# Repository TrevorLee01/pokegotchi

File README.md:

# Pokegotchi
tamagotchi project by Trevor Lee

ONSHAPE LINK: https://cad.onshape.com/documents/4788cfc2c41ccbd3b3bb658b/w/c8008663c56e0ba217e7b347/e/ed1d7d4fd3640974190b7d9b?renderMode=0&uiState=6a3ac660f6d661f4c890654a

BOM INCLUDED IN THE FILES! "BOM.csv", bottom of this README, or: https://docs.google.com/spreadsheets/d/1ZSV7nk1klidvS7acBAQEKFNUl_y9adzhBfaWMznL6cg/edit?gid=0#gid=0

______________

# What is a Pokegotchi?

This pokegotchi comes with 3 whole pokemons
- Snorlax
- Solosis
- Eevee
However, Eevee comes with 5 different types of Eeveelution depending on the exact environment (a secret). Play to find out which eeveelution you end up getting!

The possible 5 includes:
- umbreon
- leafeon
- slyveon
- glaceon
- espeon

____
# Features

The unique features of this tamagotchi are
- internal clock ( to tell between day and night)
- LDR (to tell how dark it is)

(and a completely different ESP32 :D)

____
# Why did I make it?

Through my entire childhood, I've always been into some type of media related to Pokemon. Despite being it a common hobby or interest, that never discouraged me to discontinue the love I have for Pokemon. 
I think it's such a fundamental piece to my development and I want to physically manifest the fondness by utilizing the hardware opportunity given by fallout. 

____
# Pictures‼️

Here is the pcb.

Here is the CAD.

Here is the render.

____
# How It Works ╰(°▽°)╯

Turn the Pokegotchi on and select one out of three Pokémon that you want to take care of: Snorlax, Solosis, or Eevee.

The built-in real-time clock (RTC) will help you keep track of the current time, enabling the device to know whether it is day or night. In addition, the light-dependent resistor (LDR) will detect how bright the surrounding environment is and make your Pokémon respond accordingly.

Should you pick Eevee, it will evolve into one of five unique Eeveelutions, depending both on your in-game actions and some hidden environmental factors.

Use the buttons on the Pokegotchi to navigate through the menus.

____
# How to Build Your Own Pokegotchi :D

1. Print the Case: Download the .step files from the repository and use a 3D printer to print the front case and back case.

2. Solder the Components: Solder all the components to the custom PCB, including the ESP32, RTC IC, light sensor (LDR), display, buttons, and other hardware as specified in the bill of materials.

3. Place the Hardware: Install the PCB inside the printed case using 2 M3x10 screws, and then secure the top of the case using 3 M3x5 screws. Don't forget to place the battery inside its pocket, and connect it to the pinheader.

4. Upload the Firmware: Download the .ino file from the repository and flash Pokegotchi firmware onto the ESP32.

5. Get Ready for an Exciting Journey: Turn on the device, select a Pokémon, and start training your Pokegotchi!

____
# BOM

POKEGOTCHI BILL OF MATERIALS,,,,,
 Total Cost ,,,,,
 $ 44.40 ,,,,,
,,,,,
Item, Indiv Costs ,Quanities, Cost ,Links to Order,Additional Notes
ESP32-S3-WROOM-1-N16R8 MCU, $ 6.76 ,1, $ 6.76 ,https://www.digikey.com/en/products/detail/espressif-systems/ESP32-S3-WROOM-1-N16R8/16162642,
TYPE-C-31-M-12 USB-C Receptable, $ 0.19 ,5, $ 0.93 ,https://www.lcsc.com/product-detail/C165948.html?s_z=n_q_korean%2520hroparts%2520elec%2520type-c-31-m-12&spm=wm.fly.bg.1.xh&lcsc_vid=R1cKX1cFEVUKX1ECR1FdBlRQFlAMUwFUElkPUwcDQwAxVlNeRlhZV1dRQ1dZUDsOAxUeFF5JWBYZEEoKFBINSQcJGk4%3D,"4 extra, MOQ 5"
XHXDZ 1207-P6.5MM Buzzer, $ 0.50 ,10, $ 5.03 ,https://www.aliexpress.us/item/3256810135642750.html,"9 extra, MOQ 10"
MCP73831T-2ATI/OT Charger, $ 0.76 ,1, $ 0.76 ,https://www.digikey.com/en/products/detail/microchip-technology/MCP73831T-2ATI-OT/964303?s=N4IgTCBcDaILYGMAOB2AzADjQRgCoFowBDAFwEsB6AexJAF0BfIA,
AP2112K-3.3TRG1 Voltage Regulator, $ 0.25 ,1, $ 0.25 ,https://www.digikey.com/en/products/detail/diodes-incorporated/AP2112K-3-3TRG1/4470746?s=N4IgTCBcDaIIYAcwEZlgNYFoDMA6bALgE4DmyIAugL5A,
1825910-6 Tactile Switch, $ 0.13 ,3, $ 0.39 ,https://www.digikey.com/en/products/detail/te-connectivity-alcoswitch-switches/1825910-6/1632536,
TS-104-T-A Connector, $ 1.06 ,1, $ 1.06 ,https://www.digikey.com/en/products/detail/samtec-inc/TS-104-T-A/1105490,
M20-9990246 Connector, $ 0.10 ,1, $ 0.10 ,https://www.digikey.com/en/products/detail/harwin-inc/M20-9990246/3728226?s=N4IgTCBcDaILZgAwFoCc7FgCwDYQF0BfIA,
1825910-6 Tactile Switch, $ 0.13 ,3, $ 0.39 ,https://www.digikey.com/en/products/detail/te-connectivity-alcoswitch-switches/1825910-6/1632536,
RC0805JR-075K1L Resistor, $ 0.10 ,2, $ 0.20 ,https://www.digikey.com/en/products/detail/yageo/RC0805JR-075K1L/728338,
RC0805FR-072KL Resistor, $ 0.10 ,1, $ 0.10 ,https://www.digikey.com/en/products/detail/yageo/RC0805FR-072KL/727664,
RC0805FR-0710KL Resistor, $ 0.10 ,3, $ 0.30 ,https://www.digikey.com/en/products/detail/yageo/RC0805FR-0710KL/727535,
RC0805FR-074K7L Resistor, $ 0.10 ,2, $ 0.20 ,https://www.digikey.com/en/products/detail/yageo/RC0805FR-074K7L/727929,
GL12528 LDR, $ 0.31 ,5, $ 1.56 ,https://www.lcsc.com/product-detail/C559386.html?s_z=s_p_GL12528&spm=wm.fly.bg.0.xh&lcsc_vid=Q1kKUVEAQgNbV11QQgQPV1FVRVkLV11TE1hXUwBfEgcxVlNeRVBZUFxXQlhbVjsOAxUeFF5JWBYZEEoKFBINSQcJGk4dAgUUFAk%3D,"4 extra, MOQ 5"
CL21B105KAFNNNE Capacitor, $ 0.10 ,1, $ 0.10 ,https://www.digikey.com/en/products/detail/samsung-electro-mechanics/CL21B105KAFNNNE/3886724,
CL21A475KAQNNNE Capacitor, $ 0.11 ,2, $ 0.22 ,https://www.digikey.com/en/products/detail/samsung-electro-mechanics/CL21A475KAQNNNE/3886902,
HS96L03W2C03 Screen, $ 1.87 ,1, $ 1.87 ,https://www.aliexpress.us/item/2251832337475453.html,
DS3231MZ+TRL Clock, $ 12.68 ,1, $ 12.68 ,https://www.digikey.com/en/products/detail/analog-devices-inc-maxim-integrated/DS3231MZ-TRL/2754408,
Battery, $ 6.20 ,1, $ 6.20 ,https://www.aliexpress.us/item/3256808658204287.html,
PCB, $ 0.40 ,5, $ 2.00 ,https://cart.jlcpcb.com/quote?stencilLayer=2&stencilWidth=100&stencilLength=100&stencilCounts=5&plateType=1&spm=Jlcpcb.Homepage.1010,
PLA Housing, $ -   ,, $ -   ,,
M3 x 10mm Socket Cap Head Screws, $ 0.75 ,2, $ 1.50 ,https://accu-components.com/us/metric-cap-head-screws/16004-SSCF-M3-10-12-9,
M3 x 5mm Socket Cap Head Screws, $ 0.45 ,4, $ 1.80 ,https://accu-components.com/us/metric-cap-head-screws/16001-SSCF-M3-5-12-9,4 is cheaper than 3

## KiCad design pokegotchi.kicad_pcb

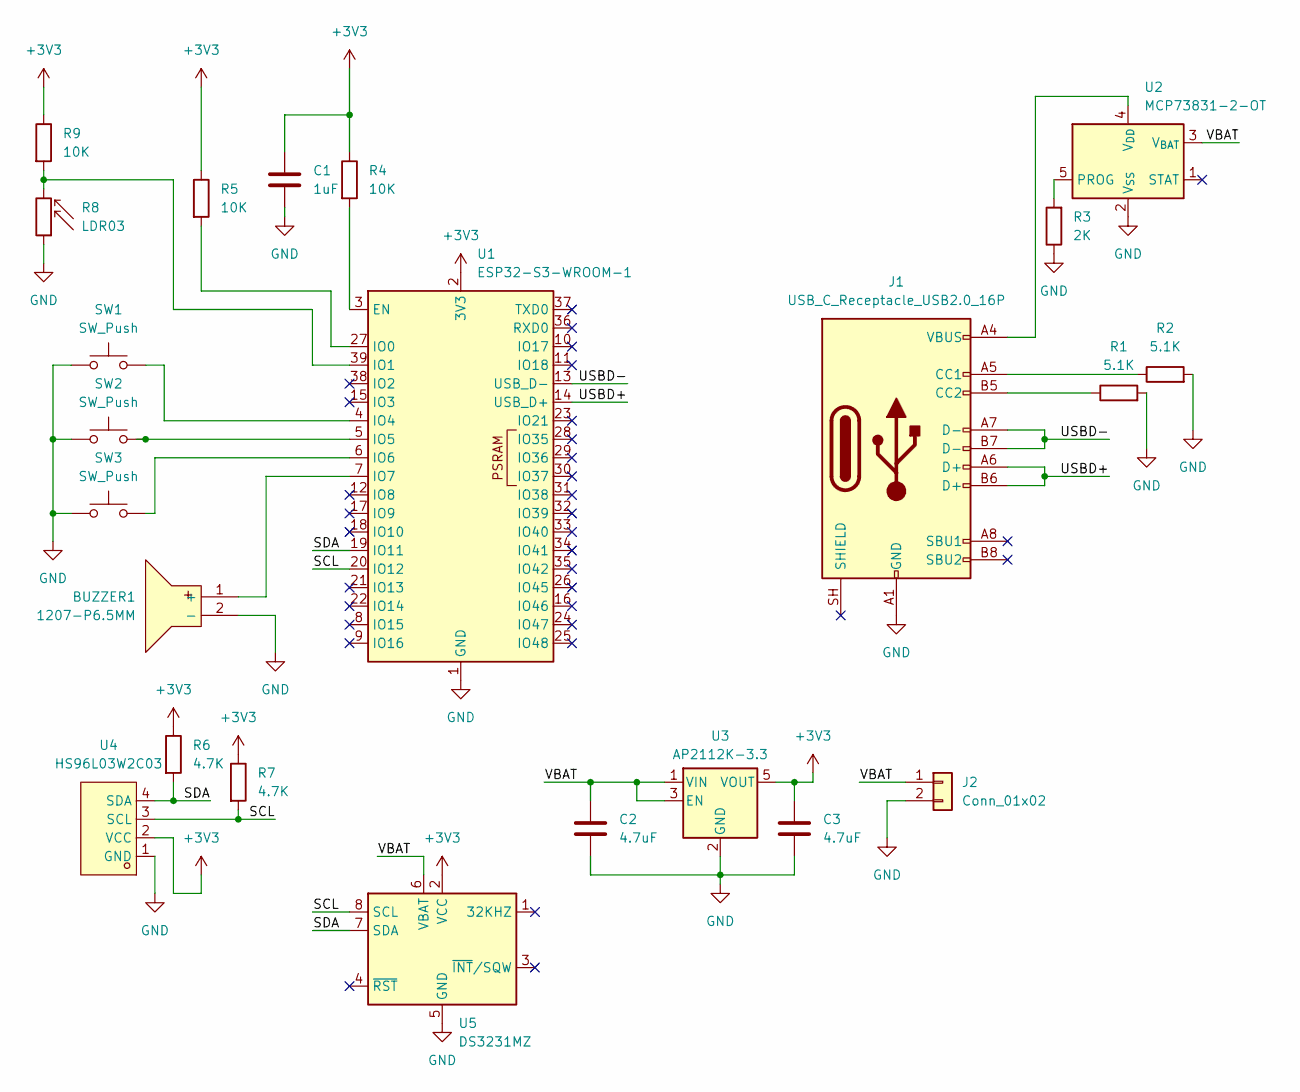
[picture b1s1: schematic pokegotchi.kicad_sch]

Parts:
BUZZER1: 1207-P6.5MM; BUZ-TH_BD12.5-P6.50-D1.4; MPN 1207-P6.5MM; LCSC Part C49246964
C1: 1uF; C_0805_2012Metric
C2, C3: 4.7uF; C_0805_2012Metric
J1: USB_C_Receptacle_USB2.0_16P; USB_C_Receptacle_HRO_TYPE-C-31-M-12
J2: Conn_01x02; PinHeader_1x02_P2.54mm_Vertical
R1, R2: 5.1K; R_0805_2012Metric
R3: 2K; R_0805_2012Metric
R4, R5, R9: 10K; R_0805_2012Metric
R6, R7: 4.7K; R_0805_2012Metric
R8: LDR03; R_LDR_10x8.5mm_P7.6mm_Vertical
SW1, SW2, SW3: SW_Push; SW_PUSH_6mm
U1: ESP32-S3-WROOM-1
U2: MCP73831-2-OT; SOT-23-5
U3: AP2112K-3.3; SOT-23-5
U4: HS96L03W2C03; OLED-TH_L27.8-W27.2-P2.54_C9900033791; MPN HS96L03W2C03; LCSC Part C5248080
U5: DS3231MZ; SOIC-8_3.9x4.9mm_P1.27mm

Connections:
+3V3: C1.1, C3.1, R4.1, R5.1, R6.1, R7.1, R9.1, U1.2 (3V3), U3.5 (VOUT), U4.2 (VCC), U5.2 (VCC)
/SCL: R7.2, U1.20 (IO12), U4.3 (SCL), U5.8 (SCL)
/SDA: R6.2, U1.19 (IO11), U4.4 (SDA), U5.7 (SDA)
/USBD+: J1.A6 (D+), J1.B6 (D+), U1.14 (USB_D+)
/USBD-: J1.A7 (D-), J1.B7 (D-), U1.13 (USB_D-)
/VBAT: C2.1, J2.1, U2.3 (V_{BAT}), U3.1 (VIN), U3.3 (EN), U5.6 (VBAT)
GND: BUZZER1.2 (-), C1.2, C2.2, C3.2, J1.A1 (GND), J1.A12 (GND), J1.B1 (GND), J1.B12 (GND), J2.2, R1.2, R2.2, R3.1, R8.1, SW1.1, SW2.1, SW3.1, U1.1 (GND), U1.40 (GND), U1.41 (GND), U2.2 (V_{SS}), U3.2 (GND), U4.1 (GND), U5.5 (GND)
unnamed: BUZZER1.1 (+), U1.7 (IO7)
unnamed: J1.A5 (CC1), R2.1
unnamed: J1.B5 (CC2), R1.1
unnamed: R4.2, U1.3 (EN)
unnamed: R5.2, U1.27 (IO0)
unnamed: R8.2, R9.2, U1.39 (IO1)
unnamed: SW1.2, U1.4 (IO4)
unnamed: SW2.2, U1.5 (IO5)
unnamed: SW3.2, U1.6 (IO6)
unnamed: R3.2, U2.5 (PROG)
unnamed: J1.A4 (VBUS), J1.A9 (VBUS), J1.B4 (VBUS), J1.B9 (VBUS), U2.4 (V_{DD})

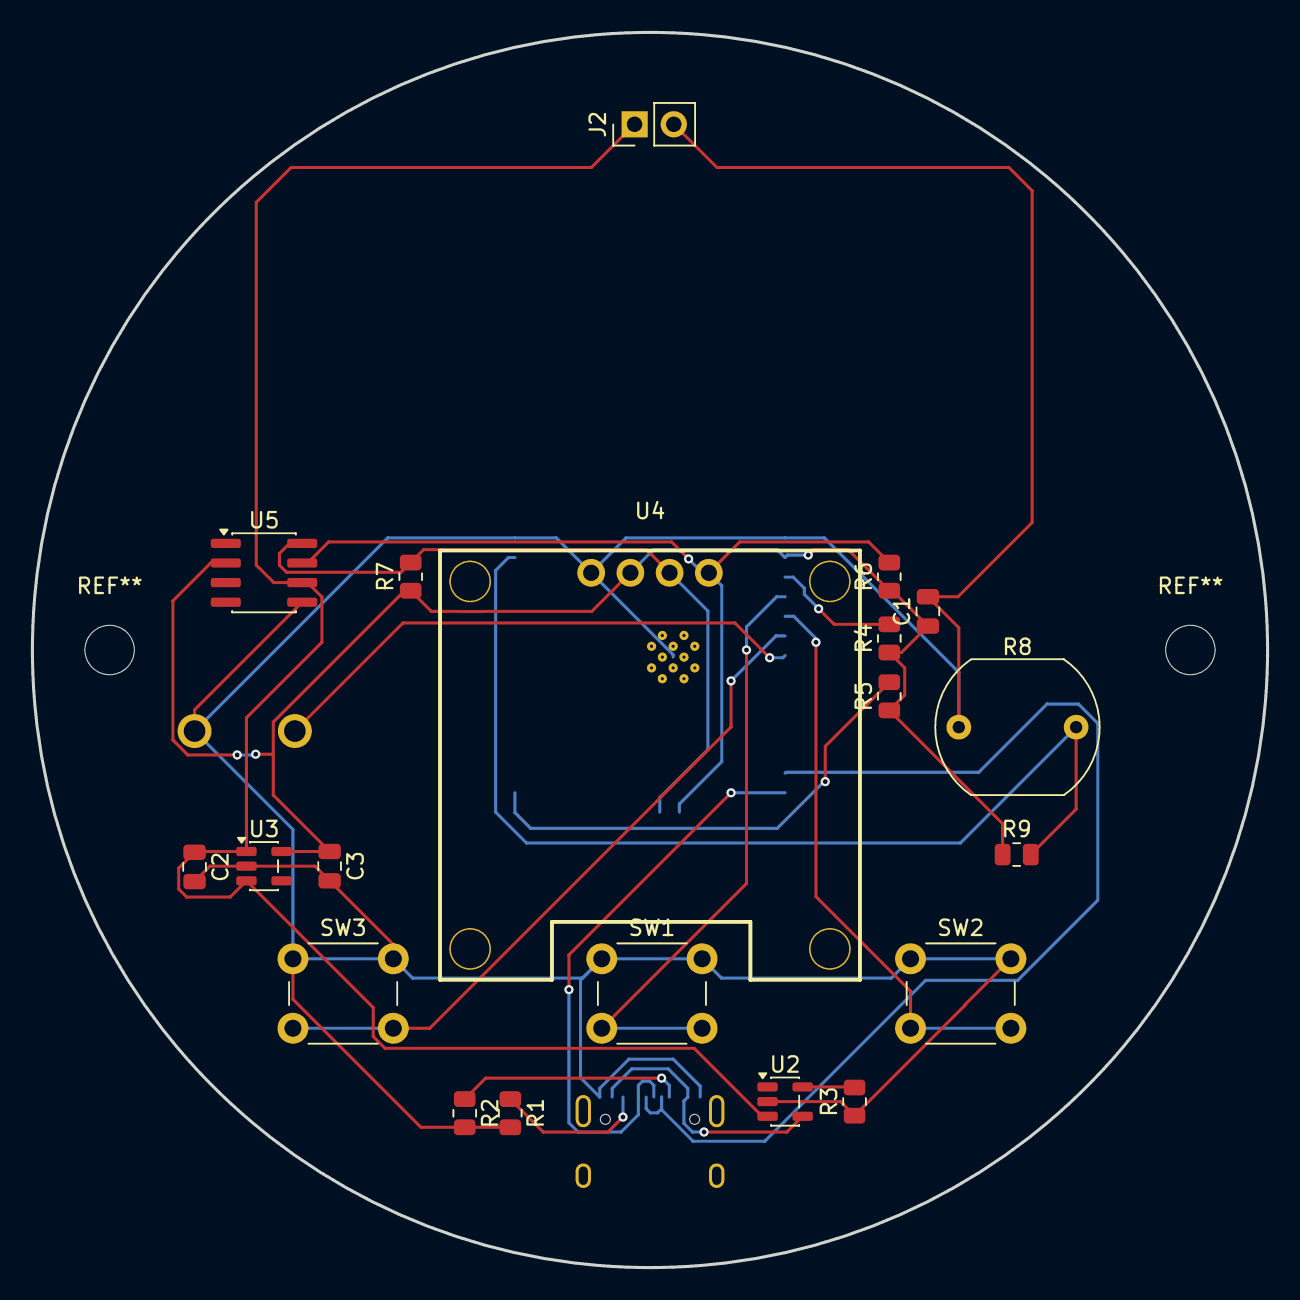
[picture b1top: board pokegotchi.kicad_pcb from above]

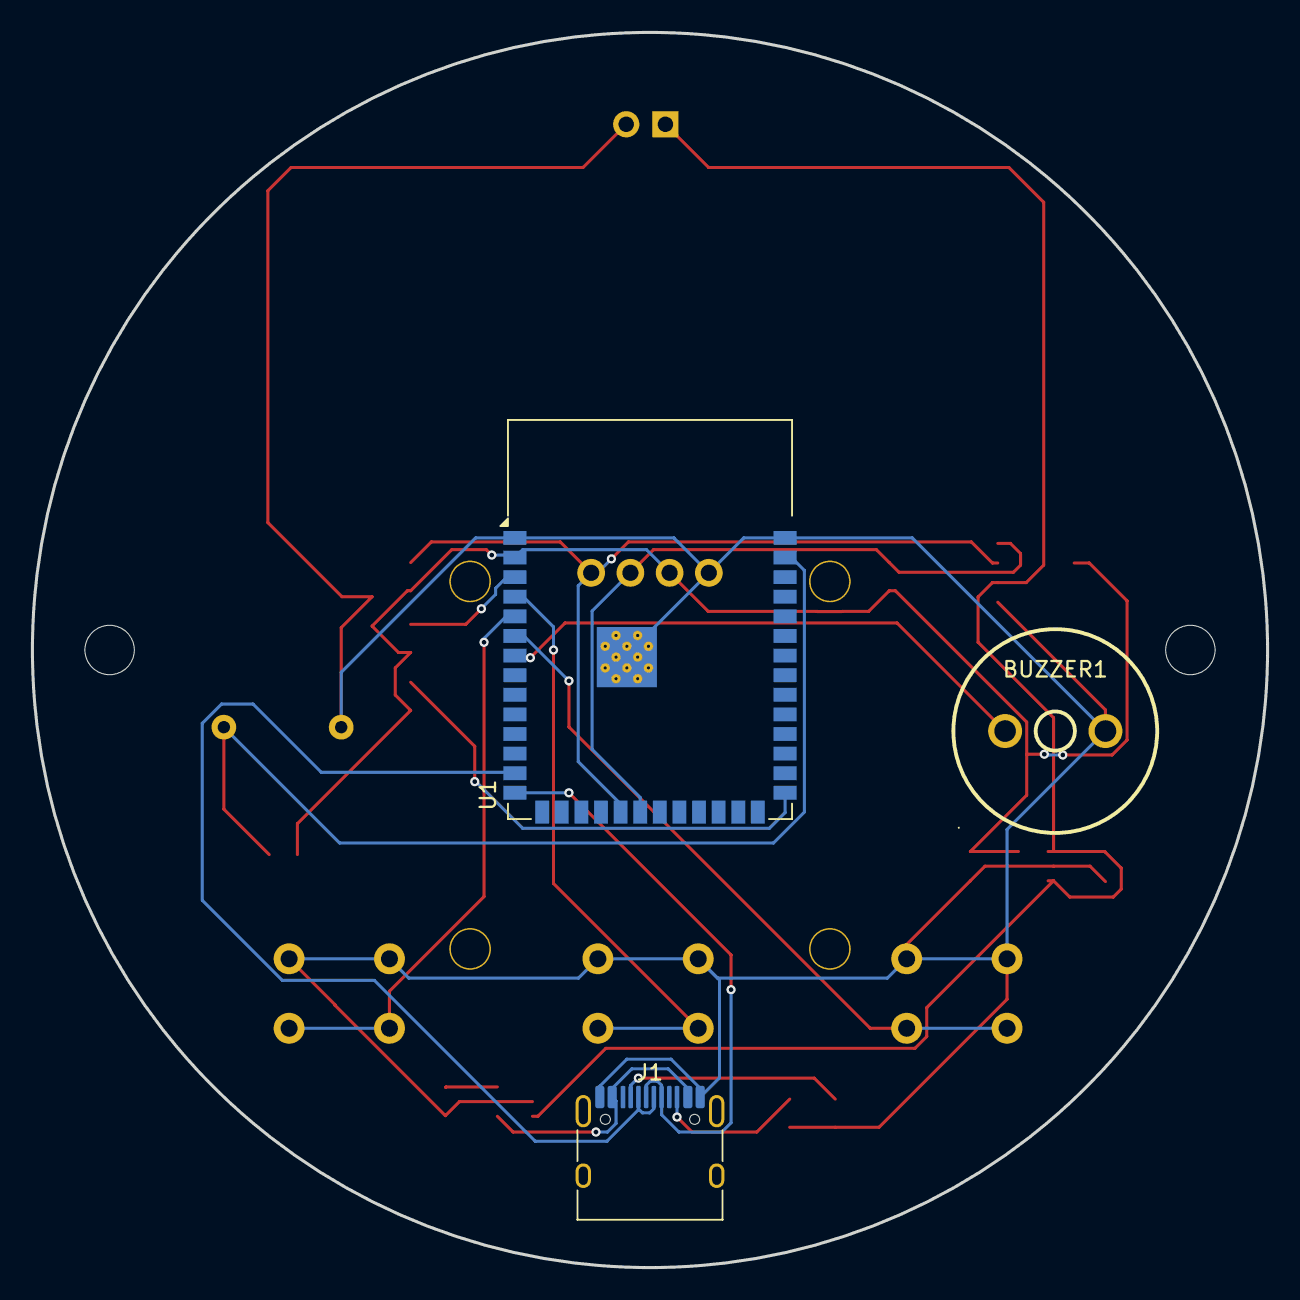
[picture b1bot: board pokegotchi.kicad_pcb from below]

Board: 2 copper layers, 80.0 x 80.0 mm, 23 parts (3 on the bottom side), 18 nets.

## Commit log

2026-06-21 sorted into files
2026-06-24 Rename Soup - Sheet1 (1).csv to BOM.csv
